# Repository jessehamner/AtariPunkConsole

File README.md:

# Atari Punk Console Implementation
##### *with modifications*

## What's In Here

- EAGLE CAD schematics 
- Detailed LaTeX documentation
- A few interesting EAGLE CAD scripts
    - at least one of which requires a script in another of my GitHub repositories
- a bill of materials for this implementation
- a python script that makes drawing 8-bit characters in EAGLE CAD pretty easy

## Where Things Are

- cad: EAGLE CAD files and the script to export images from the program
- docs: LaTeX documentation, images, and the bash script that uses ImageMagick to modify and improve the native png image exports
- graphics: EAGLE CAD scripts that draw old 8-bit characters as part of the silkscreen layers of the PCB; includes the source csv and the python script used to make the scripts

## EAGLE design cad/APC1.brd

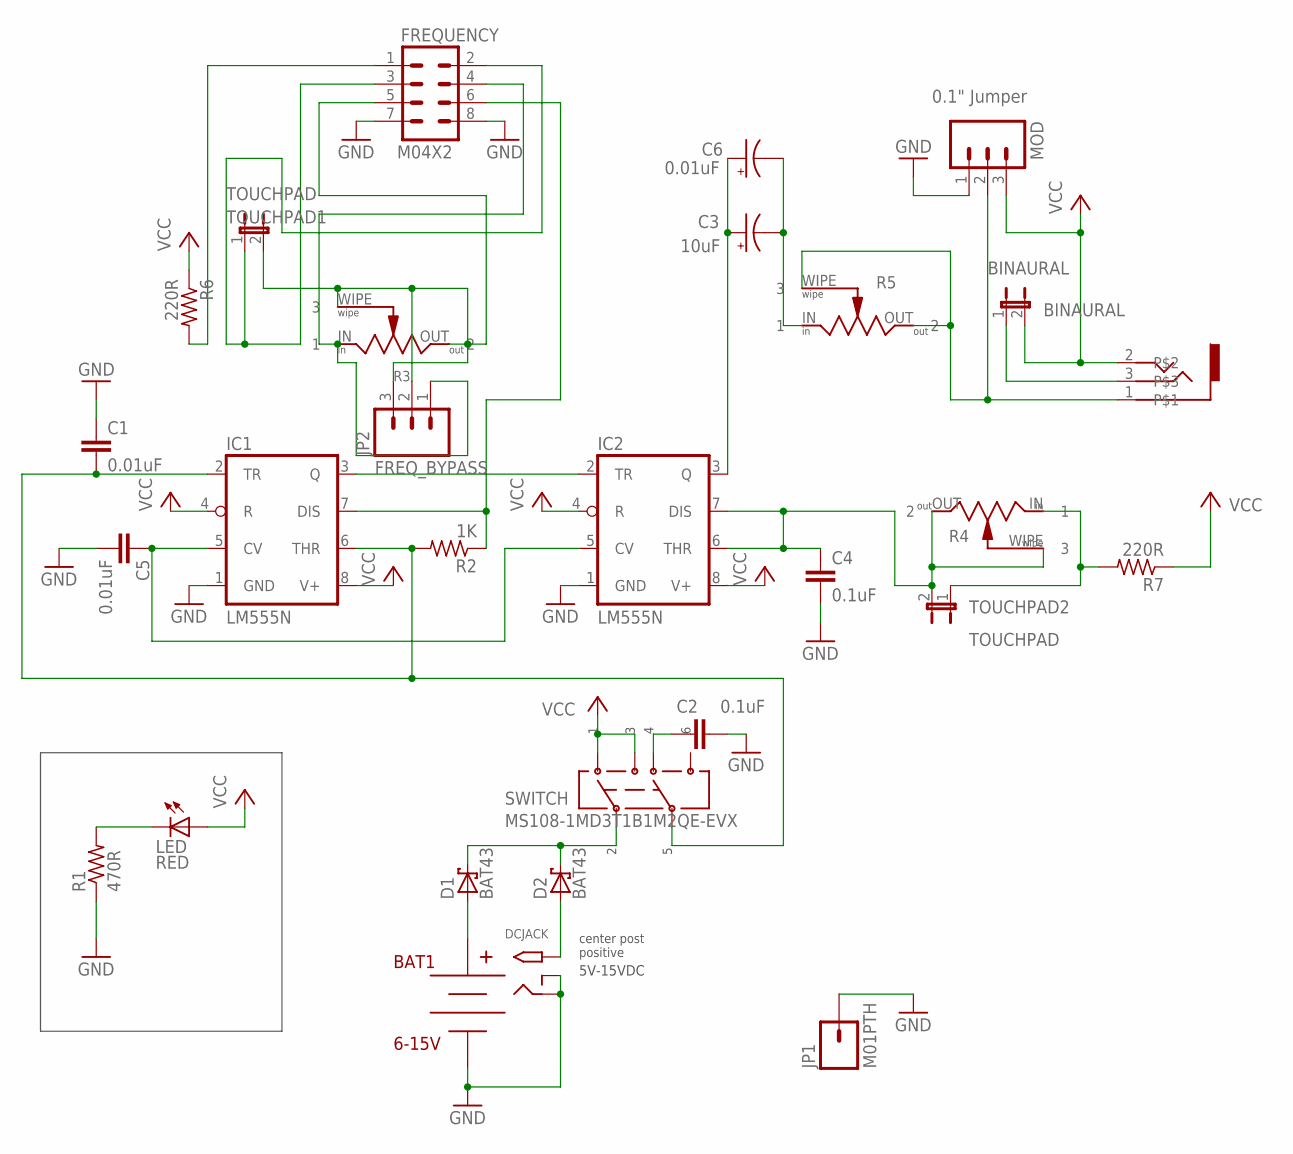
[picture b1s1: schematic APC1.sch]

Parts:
BAT1: 6-15V; BH9VPC
BINAURAL: BINAURAL; JP1
C1, C5: 0.01uF; C050-024X044
C2, C4: 0.1uF; C050-024X044
C3: 10uF; E2,5-7
C6: 0.01uF; E2,5-7
D1, D2: BAT43; DO35-7
DCJACK: PJ102A; PJ-102A
FREQUENCY: M04X2; 2X4
IC1, IC2: LM555N; DIL08
JP1: M01PTH; 1X01
JP2: FREQ_BYPASS; 1X03_SMD_RA_MALE
LED: RED; LED_LD260
LINE: SJ-3523-SMT; SJ352_AUDIOJACK
MOD: 0.1" Jumper; 1X03_LOCK
R1: 470R; 0207/7
R2: 1K; 0207/7
R3, R4, R5: CTS_UM296RE_SERIES_POTENTIOMETERUM296RE; UM296RE_POTENTIOMETER
R6, R7: 220R; 0207/7
SWITCH: MS108-1MD3T1B1M2QE-EVX
TOUCHPAD1, TOUCHPAD2: TOUCHPAD; JP1

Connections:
GND: BAT1.P$1 (V-), C1.1, C2.2, C4.2, C5.2, DCJACK.P$2 (RING), DCJACK.P$3 (RING_SW), FREQUENCY.7, FREQUENCY.8, IC1.1 (GND), IC2.1 (GND), JP1.1, MOD.1, R1.1
unnamed: FREQUENCY.5, JP2.2, JP2.3, R3.OUT (2), R3.WIPE (3), TOUCHPAD1.2
unnamed: C2.1, SWITCH.P$4 (4)
unnamed: C4.1, IC2.6 (THR), IC2.7 (DIS), R4.OUT (2), R4.WIPE (3), TOUCHPAD2.2
unnamed: IC1.3 (Q), IC2.2 (TR)
unnamed: C5.1, IC1.5 (CV), IC2.5 (CV)
unnamed: LED.K (C), R1.2
unnamed: BINAURAL.1, LINE.3
unnamed: C3.+, C6.+, IC2.3 (Q)
unnamed: C1.2, IC1.2 (TR), IC1.6 (THR), R2.2, SWITCH.P$5 (5)
unnamed: BAT1.P$2 (V+), D1.A
unnamed: D2.A, DCJACK.P$1 (TIP)
unnamed: LINE.1, MOD.2, R5.OUT (2), R5.WIPE (3)
unnamed: R4.IN (1), R7.2, TOUCHPAD2.1
unnamed: FREQUENCY.2, FREQUENCY.3, TOUCHPAD1.1
unnamed: C3.-, C6.-, R5.IN (1)
unnamed: FREQUENCY.1, R6.2
unnamed: FREQUENCY.4, JP2.1, R3.IN (1)
unnamed: FREQUENCY.6, IC1.7 (DIS), R2.1
VCC: BINAURAL.2, IC1.4 (R), IC1.8 (V+), IC2.4 (R), IC2.8 (V+), LED.A, LINE.2, MOD.3, R6.1, R7.1, SWITCH.P$1 (1), SWITCH.P$3 (3)
VIN: D1.C, D2.C, SWITCH.P$2 (2)

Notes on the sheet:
5V-15VDC
center post positive

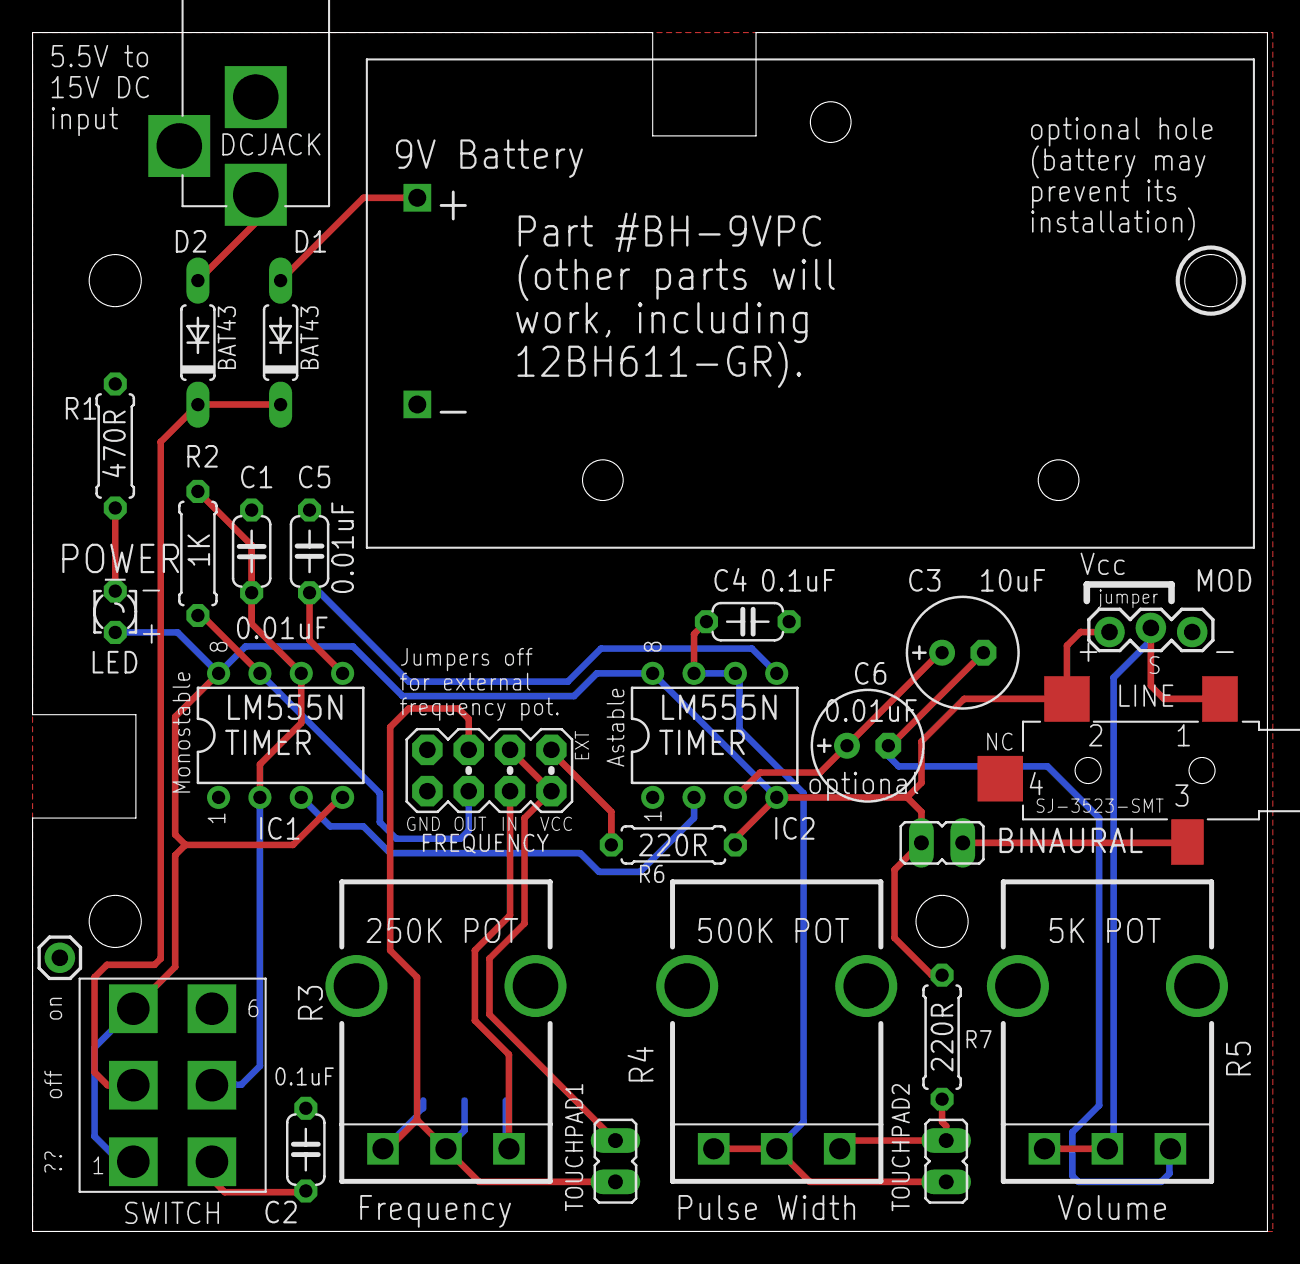
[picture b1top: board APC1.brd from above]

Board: 2 copper layers, 75.9 x 73.7 mm, 29 parts (1 on the bottom side), 21 nets.

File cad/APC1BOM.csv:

"Part","Value","Device","Package","Description","MOUSER","SPICEMODEL","SPICEPREFIX","SPICETYPE","VALUE"
"BAT1","6-15V","BH-9VPC","BH9VPC","These specs, though the battery holder is imprinted with BH-9VPC, match the specs of part number 12BH611-GR.","","","","",""
"BINAURAL","BINAURAL","JP1E","JP1","JUMPER","","","","",""
"C1","0.01uF","C-EU050-024X044","C050-024X044","CAPACITOR, European symbol","","","","",""
"C2","0.1uF","C-EU050-024X044","C050-024X044","CAPACITOR, European symbol","","","","",""
"C3","10uF","CPOL-USE2.5-7","E2,5-7","POLARIZED CAPACITOR, American symbol","","","","",""
"C4","0.1uF","C-EU050-024X044","C050-024X044","CAPACITOR, European symbol","","","","",""
"C5","0.01uF","C-EU050-024X044","C050-024X044","CAPACITOR, European symbol","","","","",""
"C6","0.1uF","C-EU050-024X044","C050-024X044","CAPACITOR, European symbol","","","","",""
"C7","0.1uF","C-EU050-024X044","C050-024X044","CAPACITOR, European symbol","","","","",""
"C8","0.01uF","CPOL-USE2.5-7","E2,5-7","POLARIZED CAPACITOR, American symbol","","","","",""
"D1","BAT43","SCHOTTKY-DIODEDO35-7","DO35-7","Schottky Diode","","","","",""
"D2","BAT43","SCHOTTKY-DIODEDO35-7","DO35-7","Schottky Diode","","","","",""
"DCJACK","PJ102A","PJ102A","PJ-102A","","","","","",""
"IC1","LM555N","LM555N","DIL08","TIMER","","","","",""
"IC2","LM555N","LM555N","DIL08","TIMER","","","","",""
"JP1","M01PTH","M01PTH","1X01","Header 1","","","","",""
"LED1","RED","LED_ELD260","LED_LD260","LED","","NONE","D","diode",""
"LINE","SJ-3523-SMT","SJ-3523-SMT","SJ352_AUDIOJACK","CUI inc Stereo Audio SMT jack, 3.5mm","","","","",""
"MOD","0.1" Jumper","M03LOCK","1X03_LOCK","Header 3","","","","",""
"R2","1K","R-US_0207/10","0207/10","RESISTOR, American symbol","","","","",""
"R3","","CTS_UM296RE_SERIES_POTENTIOMETERUM296RE","UM296RE_POTENTIOMETER","CTS UM296 RE rotary potentiometer / rheostat / varistor / variable resistor.","","","","",""
"R4","","CTS_UM296RE_SERIES_POTENTIOMETERUM296RE","UM296RE_POTENTIOMETER","CTS UM296 RE rotary potentiometer / rheostat / varistor / variable resistor.","","","","",""
"R5","","CTS_UM296RE_SERIES_POTENTIOMETERUM296RE","UM296RE_POTENTIOMETER","CTS UM296 RE rotary potentiometer / rheostat / varistor / variable resistor.","","","","",""
"R6","220R","R-US_0207/10","0207/10","RESISTOR, American symbol","","","","",""
"SWITCH","MS108-1MD3T1B1M2QE-EVX","MS108-1MD3T1B1M2QE-EVX","MS108-1MD3T1B1M2QE-EVX","Mountain Switch Toggle DPDT model 108-1MD3T1B1M2QE-EVX","108-1MD3T1B1M2QE-EVX","","","",""
"TOUCHPAD1","TOUCHPAD","JP1E","JP1","JUMPER","","","","",""
"TOUCHPAD2","TOUCHPAD","JP1E","JP1","JUMPER","","","","",""

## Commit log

2017-03-15 Initial commit. Creating repository.
2017-03-15 Deleted un-needed graphic.
2017-03-15 Modified section 8; small edits; removed images
2017-03-21 Fixed wiring on pots; more careful routing I had changed the schematic for two pots incorrectly, volume and pulse width. Added two current-limiting resistors for the freq. and pulse width pots. Spent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
2017-09-23 Cleanup and a few additions. Added PCB photo.
2017-09-25 reformatting BOM and adding part ordering info
2020-04-13 v.1.2 of board. Documentation changes / improvements.

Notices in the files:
parts and their libraries:
SparkFun-Connectors: Licensing: Creative Commons ShareAlike 4.0 International - https://creativecommons.org/licenses/by-sa/4.0
